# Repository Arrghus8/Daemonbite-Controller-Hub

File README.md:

# Daemonbite-Controller-Hub

This is an add-on board for the MiSTer FPGA project to provide original hardware inputs for SNES, NES and Genesis controllers using Daemonbite adapters (see https://github.com/MickGyver/DaemonBite-Retro-Controllers-USB). The current version serves only as a mount for the Arduinos and controller ports.

# Parts needed (v0.1):

- 2x Pro Micro ATmega32U4 (micro USB): https://www.aliexpress.com/item/1005001335338291.html
- 2x Micro USB cable: https://www.aliexpress.com/item/4000378492248.html
- 2x DB9 male port: https://www.aliexpress.com/item/33047048440.html
- 2x SNES port (90 degree): https://www.aliexpress.com/item/32838396935.html
- 2x NES port (90 degree): https://www.aliexpress.com/item/32875874969.html
- 4x M3 Male 6mm x M3 Female 20mm Standoff: https://www.aliexpress.com/item/32667773402.html

# Roadmap

- Integrate ATmega32U4 directly on board
- Integrate 7-port powered USB hub to board

# Issues

- Need to verify that 4 controllers (2x SNES and 2x NES) can be run through a single Pro Micro (see https://github.com/MickGyver/DaemonBite-Retro-Controllers-USB/issues/3).

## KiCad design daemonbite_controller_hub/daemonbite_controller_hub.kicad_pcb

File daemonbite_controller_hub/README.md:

KiCad Version: (5.99.0-9987-g41839f7e3f), release build

<code>ARDUINO PRO MICRO.STEP</code> taken from https://grabcad.com/library/arduino-pro-micro-1.

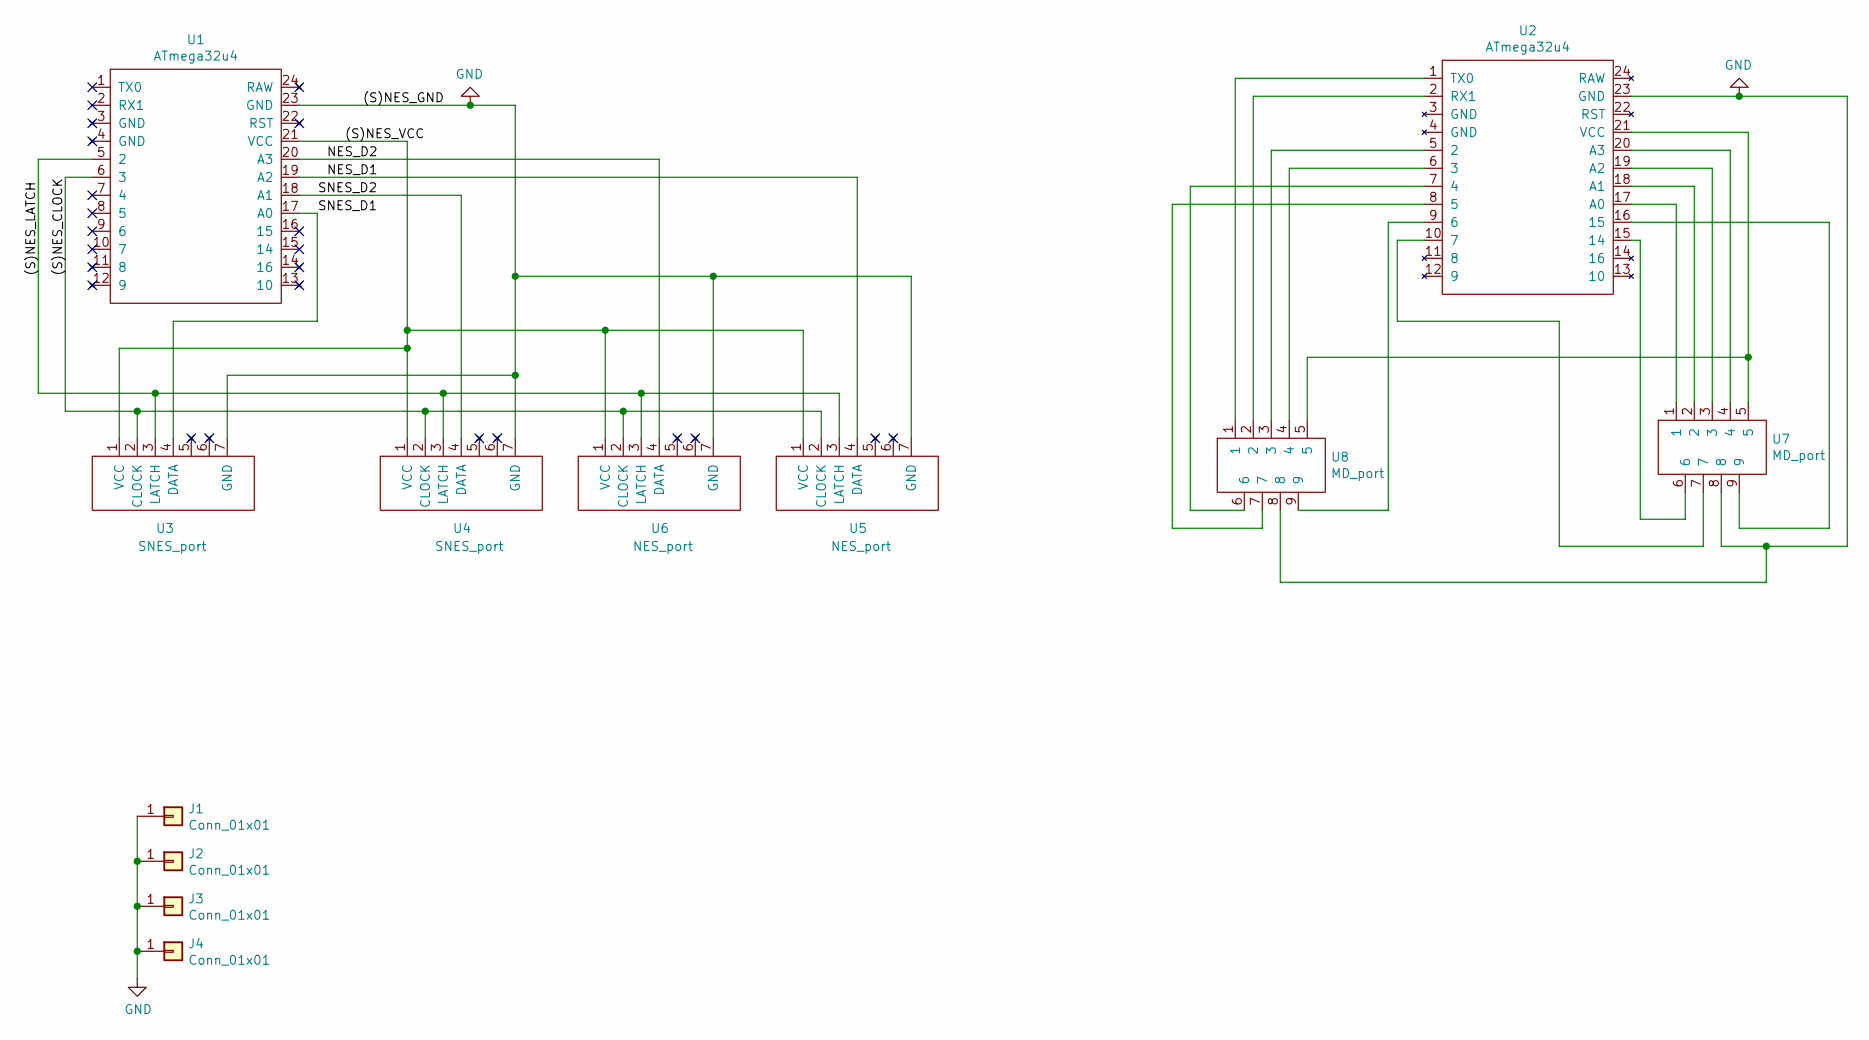
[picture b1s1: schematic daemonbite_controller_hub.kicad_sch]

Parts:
J1, J2, J3, J4: Conn_01x01; MountingHole_3.2mm_M3_Pad
U1, U2: ATmega32u4; ATmega32U4
U3, U4: SNES_port
U5, U6: NES_port
U7, U8: MD_port; DSUB-9_Male_Horizontal_P2.77x2.84mm_EdgePinOffset7.70mm_Hou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

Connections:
/(S)NES_CLOCK: U1.6 (3), U3.2 (CLOCK), U4.2 (CLOCK), U5.2 (CLOCK), U6.2 (CLOCK)
/(S)NES_LATCH: U1.5 (2), U3.3 (LATCH), U4.3 (LATCH), U5.3 (LATCH), U6.3 (LATCH)
/(S)NES_VCC: U1.21 (VCC), U3.1 (VCC), U4.1 (VCC), U5.1 (VCC), U6.1 (VCC)
/NES_D1: U1.19 (A2), U5.4 (DATA)
/NES_D2: U1.20 (A3), U6.4 (DATA)
/SNES_D1: U1.17 (A0), U3.4 (DATA)
/SNES_D2: U1.18 (A1), U4.4 (DATA)
GND: J1.1, J2.1, J3.1, J4.1, U1.23 (GND), U2.23 (GND), U3.7 (GND), U4.7 (GND), U5.7 (GND), U6.7 (GND), U7.8, U8.8
unnamed: U2.1 (TX0), U8.1
unnamed: U2.2 (RX1), U8.2
unnamed: U2.5 (2), U8.3
unnamed: U2.6 (3), U8.4
unnamed: U2.7 (4), U8.6
unnamed: U2.8 (5), U8.7
unnamed: U2.9 (6), U8.9
unnamed: U2.10 (7), U7.7
unnamed: U2.15 (14), U7.6
unnamed: U2.16 (15), U7.9
unnamed: U2.17 (A0), U7.1
unnamed: U2.18 (A1), U7.2
unnamed: U2.19 (A2), U7.3
unnamed: U2.20 (A3), U7.4
unnamed: U2.21 (VCC), U7.5, U8.5

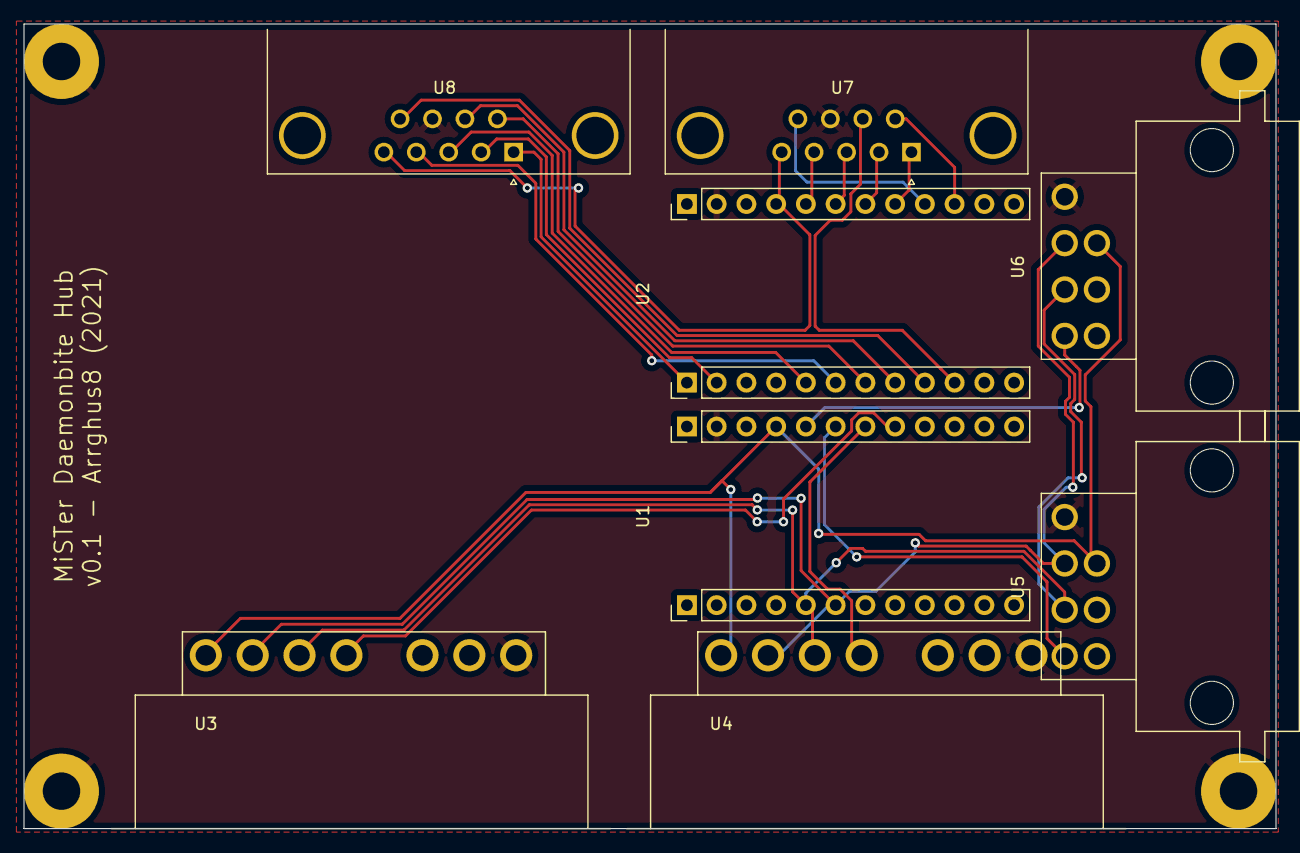
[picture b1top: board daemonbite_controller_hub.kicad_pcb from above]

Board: 2 copper layers, 106.9 x 68.7 mm, 12 parts (0 on the bottom side), 23 nets.
